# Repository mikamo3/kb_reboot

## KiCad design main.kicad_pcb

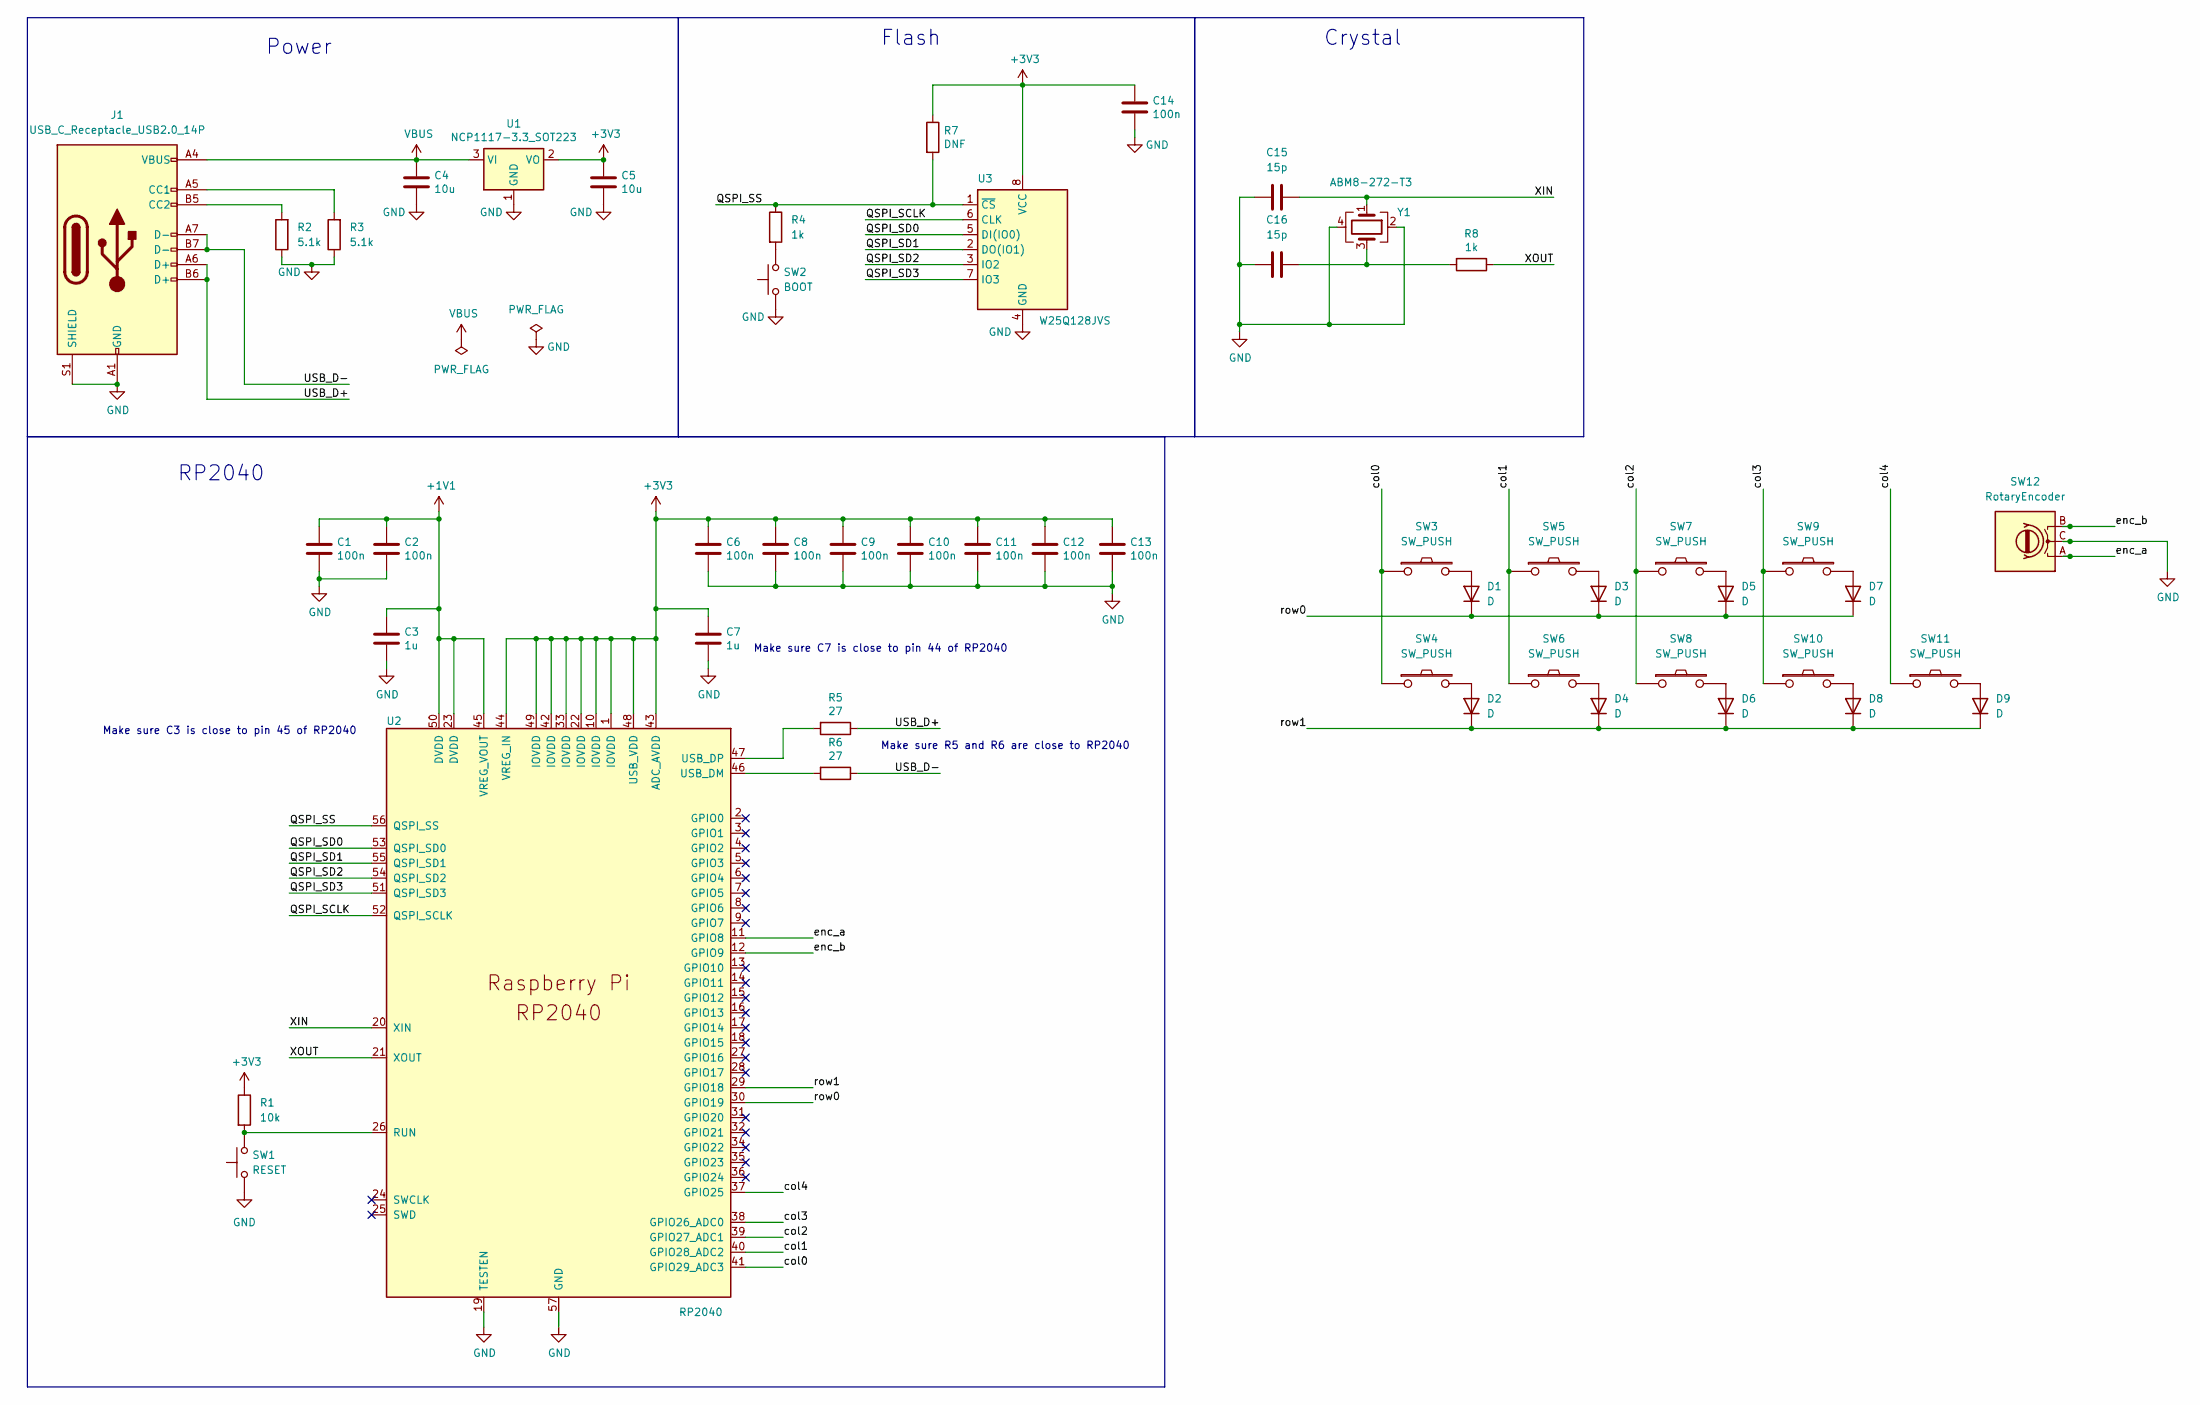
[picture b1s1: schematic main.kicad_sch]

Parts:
C1, C2, C6, C8, C9, C10, C11, C12, C13, C14: 100n; C_0402_1005Metric; LCSC C307331
C3, C7: 1u; C_0402_1005Metric; LCSC C52923
C4, C5: 10u; C_0805_2012Metric; LCSC C15850
C15, C16: 15p; C_0603_1608Metric; LCSC C1644
D1, D2, D3, D4, D5, D6, D7, D8, D9: D; Diode_SOD123; LCSC C81598
J1: USB_C_Receptacle_USB2.0_14P; USB_C_Receptacle_Palconn_UTC16-G; LCSC C2988369
R1: 10k; R_0402_1005Metric; LCSC C25744
R2, R3: 5.1k; R_0402_1005Metric; LCSC C25905
R4, R8: 1k; R_0402_1005Metric; LCSC C11702
R5, R6: 27; R_0603_1608Metric; LCSC C25190
R7: DNF; R_0402_1005Metric
SW1: RESET; Tact_Switch_5.1_5.1mm_SMD; LCSC C318884
SW2: BOOT; Tact_Switch_5.1_5.1mm_SMD; LCSC C318884
SW3, SW4, SW5, SW6, SW7, SW8, SW9, SW10: SW_PUSH; SW_ChocV1_Hotswap_1.0u
SW11: SW_PUSH; SW_ChocV1_Hotswap_1.50u
SW12: RotaryEncoder; RotaryEncoder_Alps_EC12E_Vertical_H20mm
U1: NCP1117-3.3_SOT223; SOT-223-3_TabPin2; LCSC C6186
U2: RP2040; RP2040-QFN-56; LCSC C2040
U3: W25Q128JVS; SOIC-8_5.23x5.23mm_P1.27mm; LCSC C97521
Y1: ABM8-272-T3; Crystal_SMD_3225-4Pin_3.2x2.5mm; LCSC C9002

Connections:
+1V1: C1.1, C2.1, C3.1, U2.23 (DVDD), U2.45 (VREG_VOUT), U2.50 (DVDD)
+3V3: C5.1, C6.1, C7.1, C8.1, C9.1, C10.1, C11.1, C12.1, C13.1, C14.1, R1.1, R7.1, U1.2 (VO), U2.1 (IOVDD), U2.10 (IOVDD), U2.22 (IOVDD), U2.33 (IOVDD), U2.42 (IOVDD), U2.43 (ADC_AVDD), U2.44 (VREG_IN), U2.48 (USB_VDD), U2.49 (IOVDD), U3.8 (VCC)
/QSPI_SCLK: U2.52 (QSPI_SCLK), U3.6 (CLK)
/QSPI_SD0: U2.53 (QSPI_SD0), U3.5 (DI(IO0))
/QSPI_SD1: U2.55 (QSPI_SD1), U3.2 (DO(IO1))
/QSPI_SD2: U2.54 (QSPI_SD2), U3.3 (IO2)
/QSPI_SD3: U2.51 (QSPI_SD3), U3.7 (IO3)
/QSPI_SS: R4.1, R7.2, U2.56 (QSPI_SS), U3.1 (~CS)
/USB_D+: J1.A6 (D+), J1.B6 (D+), R5.1
/USB_D-: J1.A7 (D-), J1.B7 (D-), R6.1
/XIN: C15.2, U2.20 (XIN), Y1.1
/XOUT: R8.1, U2.21 (XOUT)
/col0: SW3.1, SW4.1, U2.41 (GPIO29_ADC3)
/col1: SW5.1, SW6.1, U2.40 (GPIO28_ADC2)
/col2: SW7.1, SW8.1, U2.39 (GPIO27_ADC1)
/col3: SW9.1, SW10.1, U2.38 (GPIO26_ADC0)
/col4: SW11.1, U2.37 (GPIO25)
/enc_a: SW12.A, U2.11 (GPIO8)
/enc_b: SW12.B, U2.12 (GPIO9)
/row0: D1.1 (K), D3.1 (K), D5.1 (K), D7.1 (K), U2.30 (GPIO19)
/row1: D2.1 (K), D4.1 (K), D6.1 (K), D8.1 (K), D9.1 (K), U2.29 (GPIO18)
GND: C1.2, C2.2, C3.2, C4.2, C5.2, C6.2, C7.2, C8.2, C9.2, C10.2, C11.2, C12.2, C13.2, C14.2, C15.1, C16.1, J1.A1 (GND), J1.A12 (GND), J1.B1 (GND), J1.B12 (GND), J1.S1 (SHIELD), R2.1, R3.1, SW1.1, SW1.2, SW2.1, SW2.2, SW12.C, U1.1 (GND), U2.19 (TESTEN), U2.57 (GND), U3.4 (GND), Y1.2, Y1.4
unnamed: C16.2, R8.2, Y1.3
unnamed: D1.2 (A), SW3.2
unnamed: D2.2 (A), SW4.2
unnamed: D3.2 (A), SW5.2
unnamed: D4.2 (A), SW6.2
unnamed: D5.2 (A), SW7.2
unnamed: D6.2 (A), SW8.2
unnamed: D7.2 (A), SW9.2
unnamed: D8.2 (A), SW10.2
unnamed: D9.2 (A), SW11.2
unnamed: J1.A5 (CC1), R3.2
unnamed: J1.B5 (CC2), R2.2
unnamed: R4.2, SW2.3, SW2.4
unnamed: R1.2, SW1.3, SW1.4, U2.26 (RUN)
unnamed: R6.2, U2.46 (USB_DM)
unnamed: R5.2, U2.47 (USB_DP)
VBUS: C4.1, J1.A4 (VBUS), J1.A9 (VBUS), J1.B4 (VBUS), J1.B9 (VBUS), U1.3 (VI)

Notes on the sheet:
Power
Make sure R5 and R6 are close to RP2040
Flash
Crystal
RP2040
Make sure C3 is close to pin 45 of RP2040
Make sure C7 is close to pin 44 of RP2040

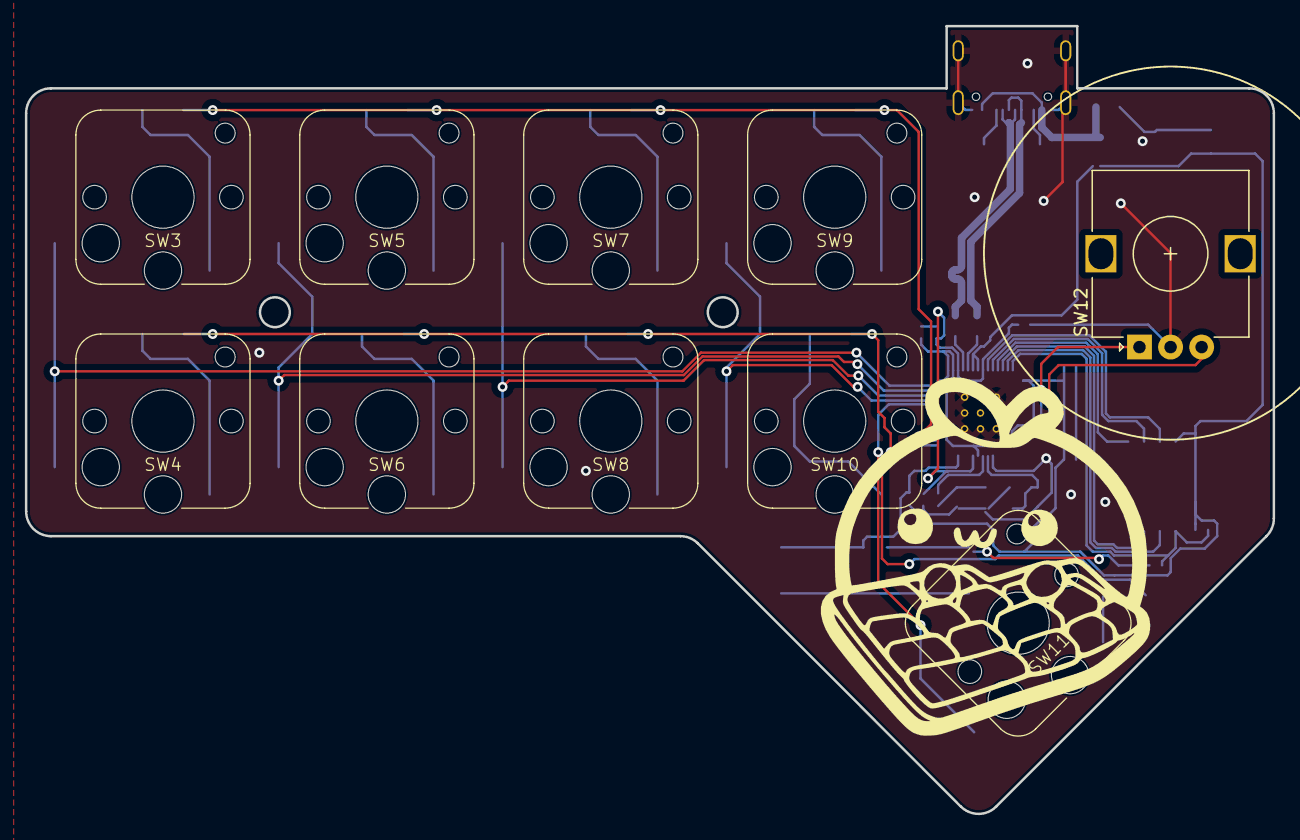
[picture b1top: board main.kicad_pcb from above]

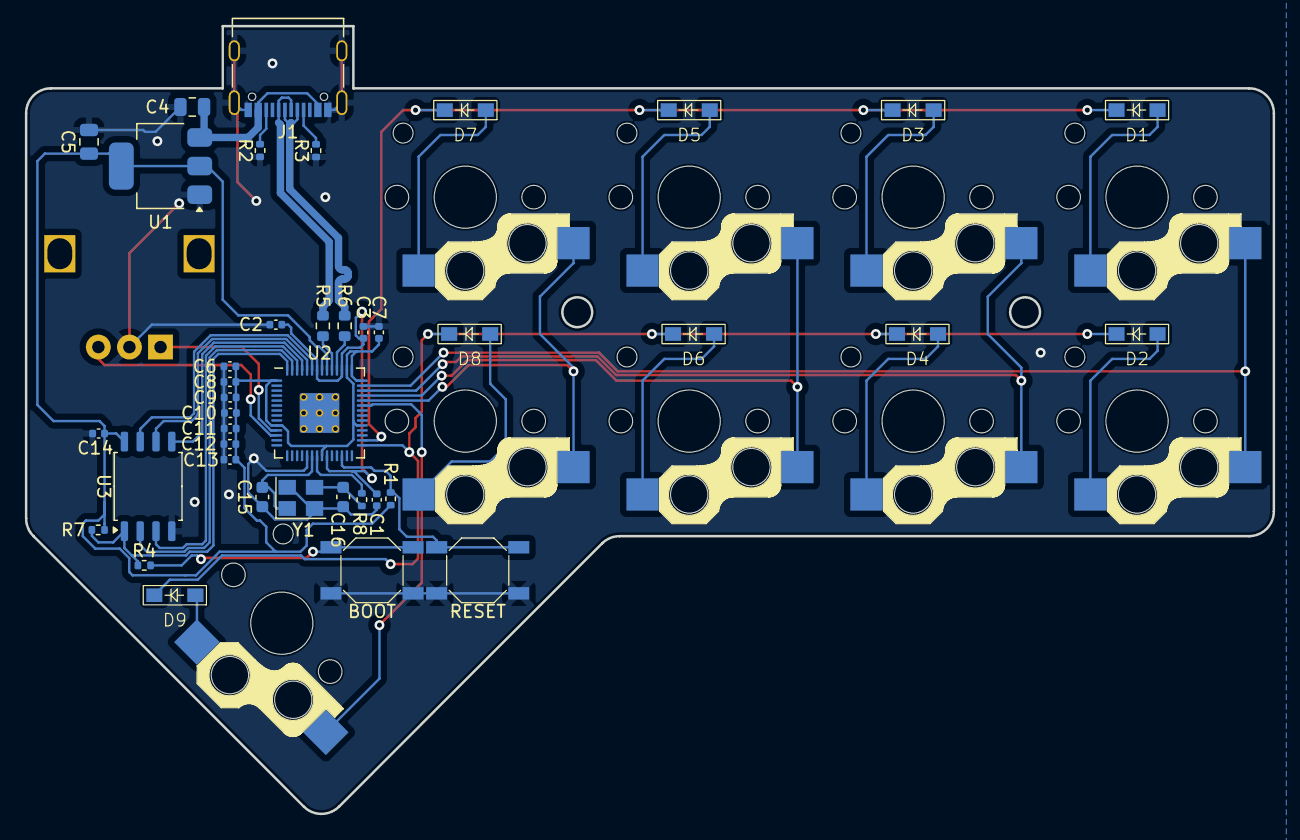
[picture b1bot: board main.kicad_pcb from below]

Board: 2 copper layers, 100.3 x 63.3 mm, 50 parts (40 on the bottom side), 39 nets.

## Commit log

2024-03-02 :sparkles: (all) init
2024-03-02 :sparkles: (all) (all) ready for manufacturing
2024-08-27 :sparkles: (all) prepare fab
2024-08-27 :arrow_up: (lib) commit lib
2024-10-29 :bug: (chore)
2024-10-29 :bug: (fix capacitor)
